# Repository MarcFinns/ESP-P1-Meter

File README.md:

# P1 Meter

- Attaches to the standard P1 port of Dutch smart meters
- Powered via the P1 port (no power supply needed)
- Can be invoked via HTTP from any home automation system via REST API
- Readings in JSON format via via **/readMeter** endpoint
- Reboot via **/reboot** endpoint
- Status can be visualised via **/settings** endpoing
- Integrates WifiManager for network selection without hardcoding credentials
- Integrates ArduinoOTA for updates without cable

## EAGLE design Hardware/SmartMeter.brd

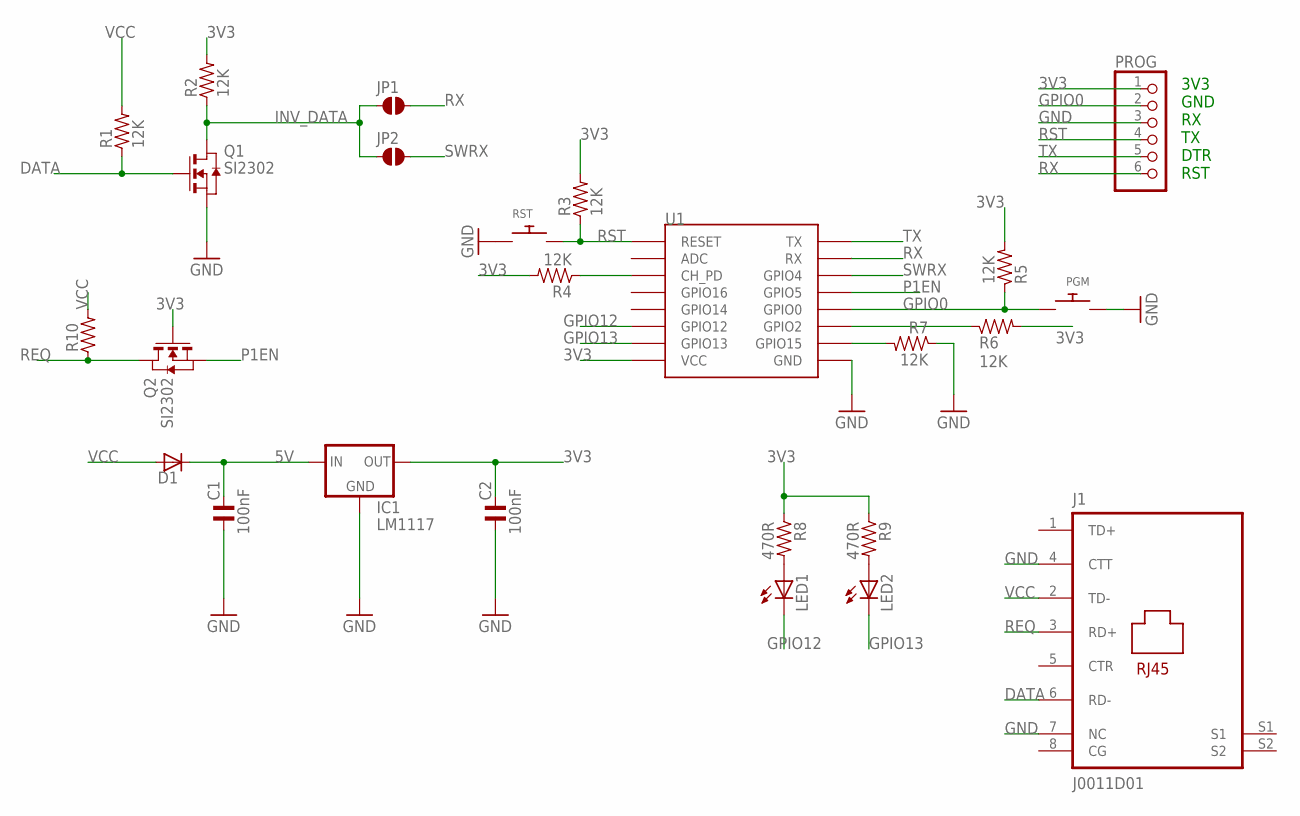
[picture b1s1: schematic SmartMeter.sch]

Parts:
C1, C2: 100nF; C0805MP
D1: DIODE_SOD-123FL; SOD-123FL
IC1: LM1117; SOT223
J1: J0011D01; J0-C/D/E
JP1, JP2: SJ-035
LED1, LED2: LEDCHIPLED_0805; CHIPLED_0805
PGM: SWITCH_PUSHBUTTONC&K_KSS; BTN_CK_KSS
PROG: PINHD-1X6B; 1X06-BIG
Q1, Q2: SI2302; SOT-23
R1, R2, R3, R4, R5, R6, R7: 12K; 0805_RES
R8, R9: 470R; 0805_RES
R10: RESISTOR0805_RES; 0805_RES
RST: SWITCH_PUSHBUTTONC&K_KSS; BTN_CK_KSS
U1: ESP12

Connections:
3V3: C2.2, IC1.2 (OUT), PROG.1, Q2.3 (G), R2.2, R3.2, R4.2, R5.2, R6.2, R8.1, R9.1, U1.VCC
5V: C1.2, D1.C, IC1.3 (IN)
DATA: J1.6 (RD-), Q1.3 (G), R1.1
GND: C1.1, C2.1, IC1.1 (GND), J1.4 (CTT), J1.7 (NC), PGM.P$1, PROG.3, Q1.2 (S), R7.1, RST.P$1, U1.GND
GPIO0: PGM.P$2, PROG.2, R5.1, U1.GPIO0
GPIO12: LED1.C, U1.GPIO12
GPIO13: LED2.C, U1.GPIO13
INV_DATA: JP1.1, JP2.1, Q1.1 (D), R2.1
unnamed: R4.1, U1.CH_PD
unnamed: R7.2, U1.GPIO15
unnamed: R6.1, U1.GPIO2
unnamed: LED1.A, R8.2
unnamed: LED2.A, R9.2
P1EN: Q2.2 (S), U1.GPIO5
REQ: J1.3 (RD+), Q2.1 (D), R10.1
RST: PROG.4, R3.1, RST.P$2, U1.RESET
RX: JP1.2, PROG.6, U1.RX
SWRX: JP2.2, U1.GPIO4
TX: PROG.5, U1.TX
VCC: D1.A, J1.2 (TD-), R1.2, R10.2

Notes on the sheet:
3V3 GND RX TX DTR RST

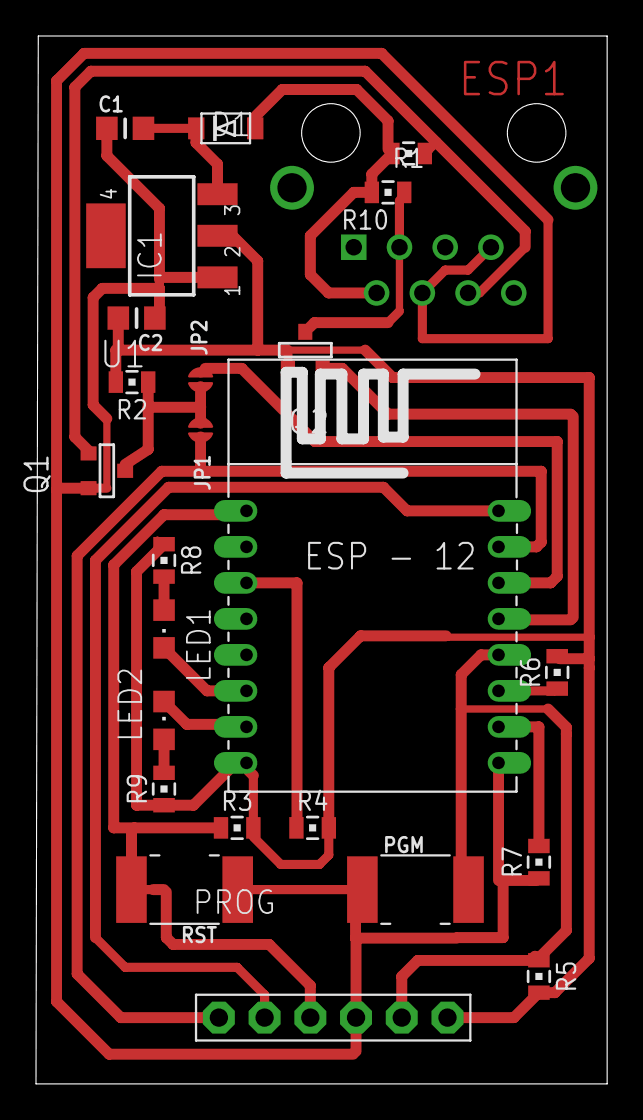
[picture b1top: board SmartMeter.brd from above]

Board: 2 copper layers, 31.7 x 58.2 mm, 25 parts (1 on the bottom side), 20 nets.

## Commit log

2021-06-16 Working version
2021-06-16 Cleanup

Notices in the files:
parts and their libraries:
rc-master-smd: Copyright (C) 2007-2008, Bob Starr
pulse-eng: Copyright (C) 2011, Bob Starr
jumpers: Copyright (C) 2009, Bob Starr
